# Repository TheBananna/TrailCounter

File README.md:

# TrailCounter
 A CV based trail counter I designed in a school group for the Friends of the Huckleberry Trail. Our final report can be found [here.](https://docs.google.com/document/d/190Tmrp1QDY-CEp3unXKZ8hlU1ujgZfHA_XcbUgvdIYQ/edit?usp=sharing)

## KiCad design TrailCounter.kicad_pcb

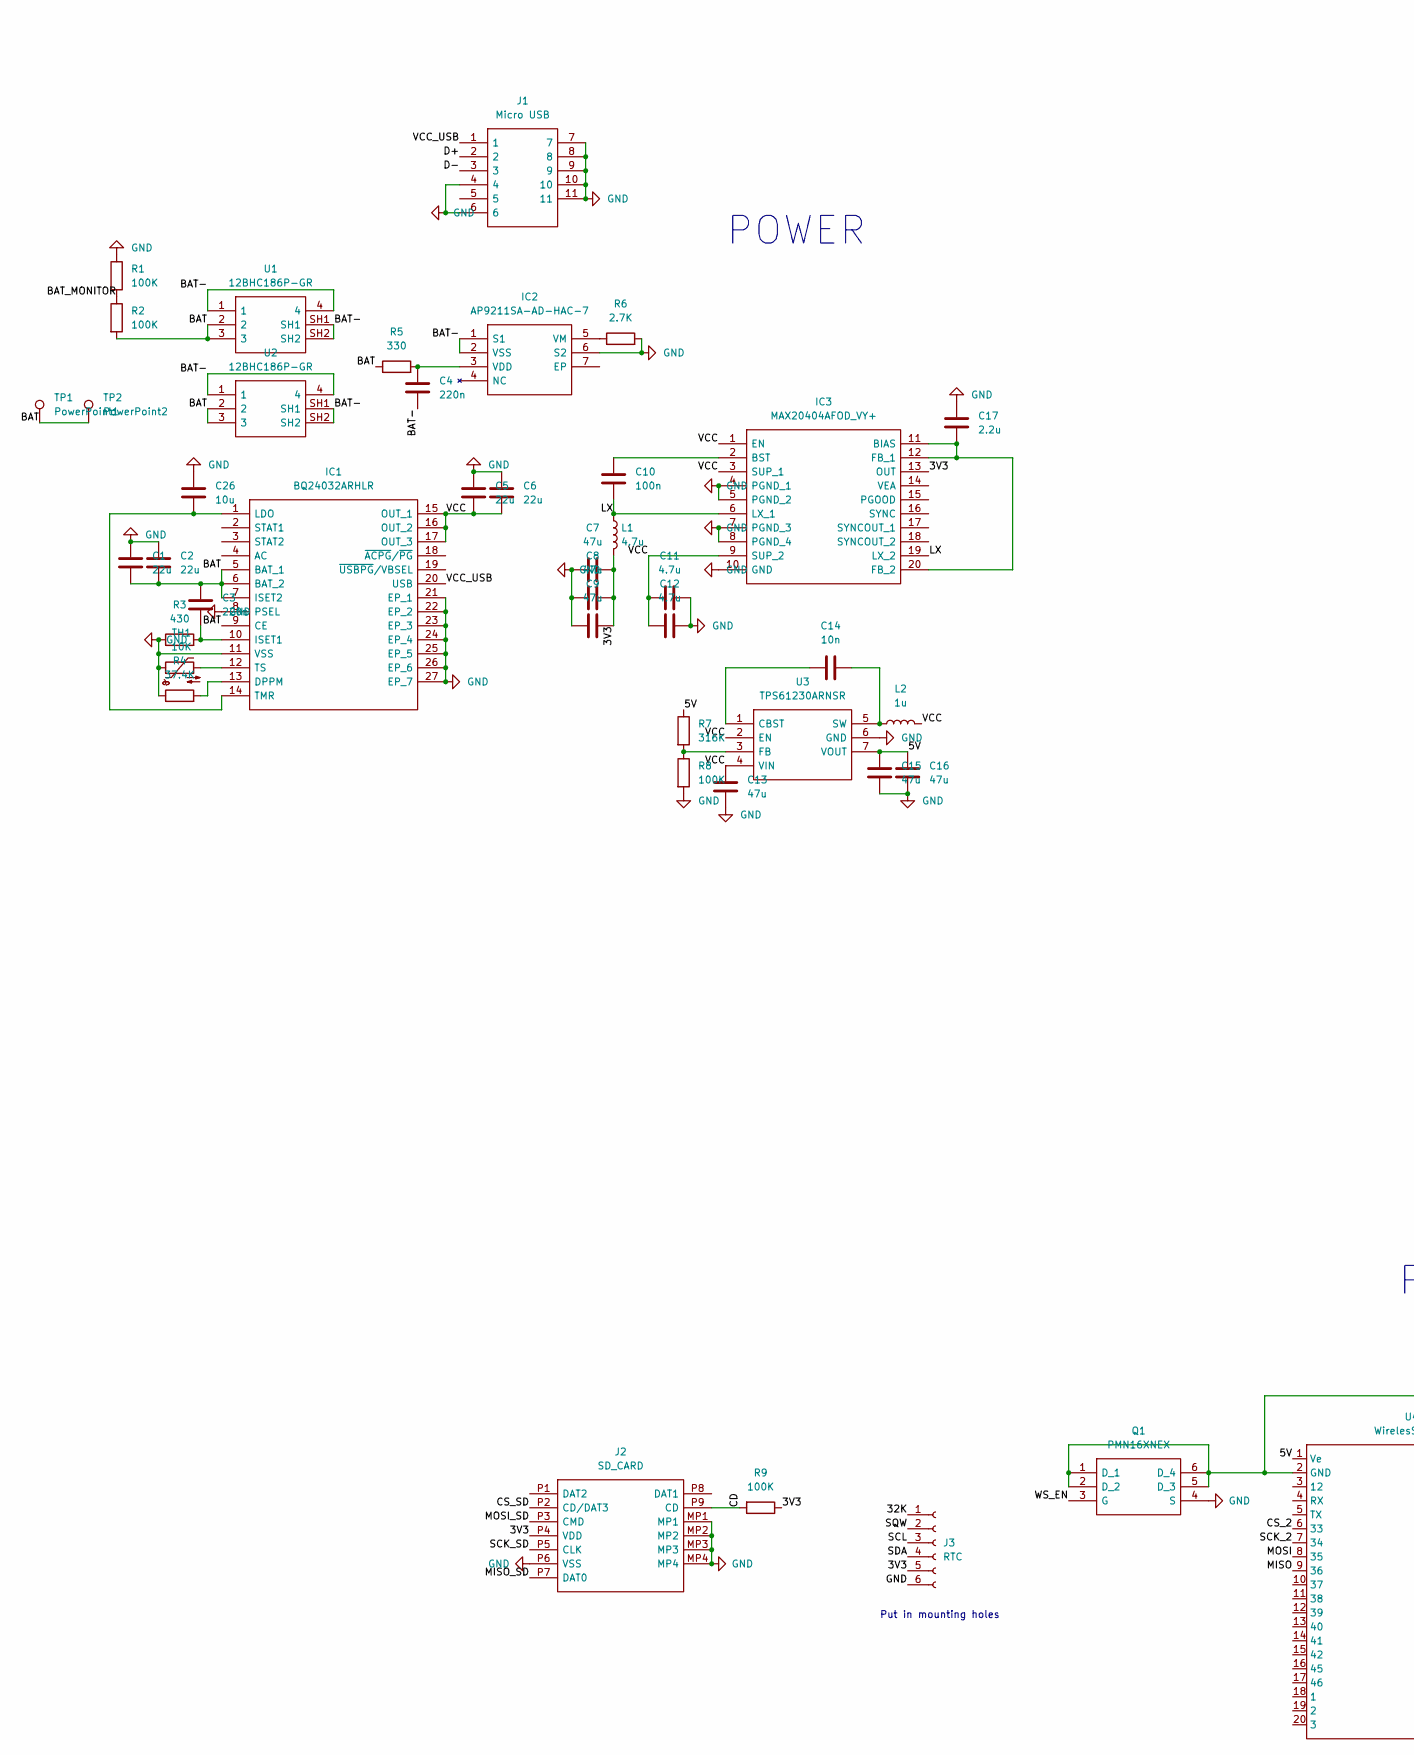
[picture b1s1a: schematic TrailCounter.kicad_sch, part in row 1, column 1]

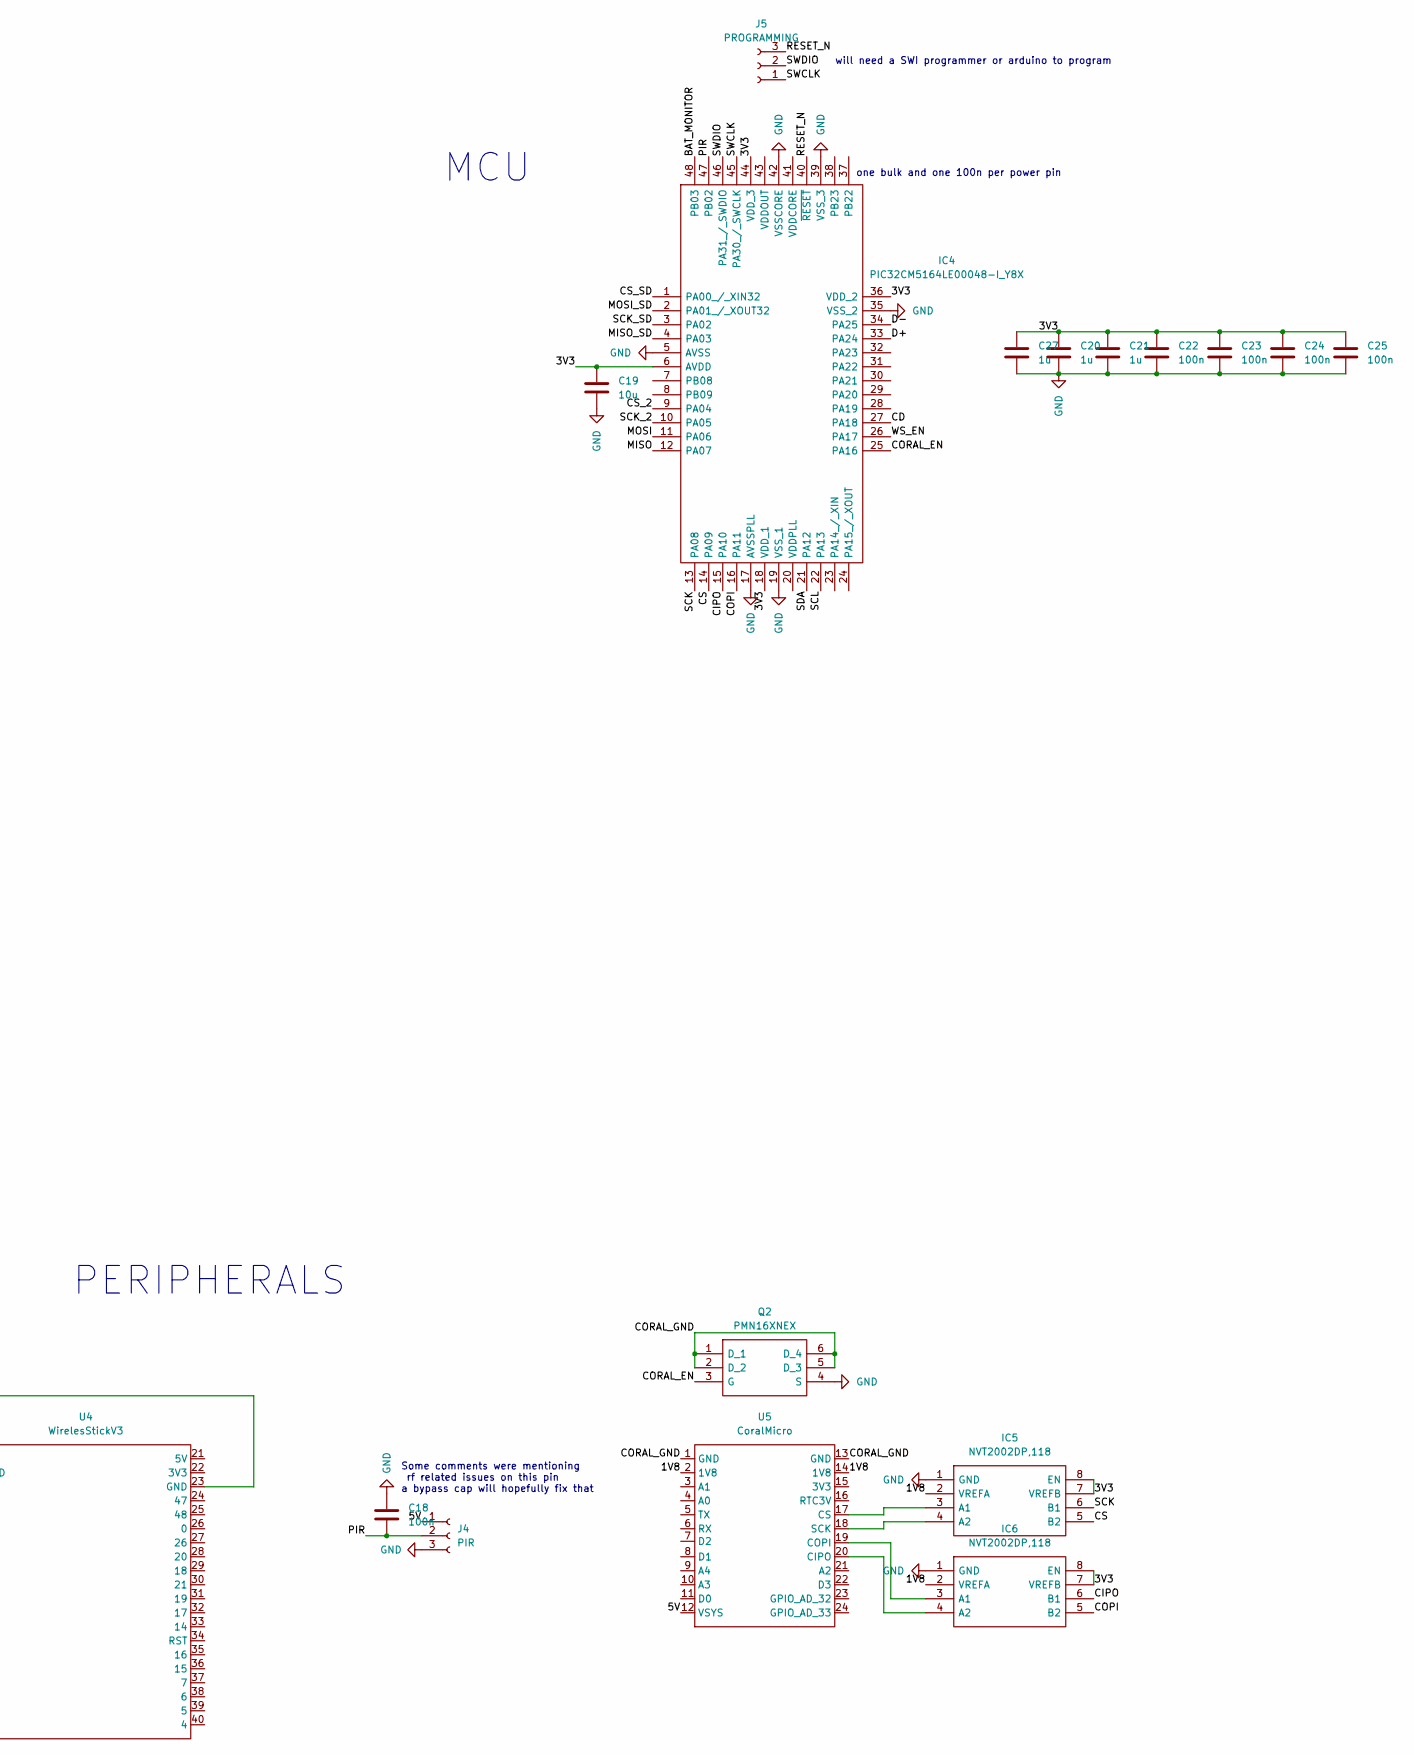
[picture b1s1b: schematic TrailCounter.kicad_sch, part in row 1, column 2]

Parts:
C1, C2, C5, C6: 22u; C_0805_2012Metric
C3, C4: 220n; C_0402_1005Metric
C7, C8, C9, C13, C15, C16: 47u; C_0805_2012Metric
C10, C18, C22, C23, C24, C25: 100n; C_0402_1005Metric
C11, C12: 4.7u; C_0603_1608Metric
C14: 10n; C_0402_1005Metric
C17: 2.2u; C_0603_1608Metric
C19, C26: 10u; C_0805_2012Metric
C20, C21, C27: 1u; C_0402_1005Metric
IC1: BQ24032ARHLR; MSP430FR2522IRHLR; Mouser Part Number 595-BQ24032ARHLR
IC2: AP9211SA-AD-HAC-7; AP9211SAADHAC7; Mouser Part Number 621-AP9211SA-AD-HAC7
IC3: MAX20404AFOD_VY+; MAX20404AFODVY; Mouser Part Number 700-MAX20404AFOD/VY+
IC4: PIC32CM5164LE00048-I_Y8X; QFP50P900X900X120-48N; Mouser Part Number 579-M5164LE00048IY8X
IC5, IC6: NVT2002DP,118; SOP65P490X110-8N; Mouser Part Number 771-NVT2002DP118
J1: Micro USB; UJ2WMIBH4SMTTR; Mouser Part Number 490-UJ2W-MIBH-4-SMT
J2: SD_CARD; MEM20750014001A; Mouser Part Number 640-MEM20750014001A
J3: RTC; PinHeader_1x06_P2.54mm_Vertical
J4: PIR; PinHeader_1x03_P2.54mm_Vertical
J5: PROGRAMMING; PinHeader_1x03_P2.54mm_Vertical
L1: 4.7u; L_12x12mm_H6mm
L2: 1u; L_1210_3225Metric
Q1, Q2: PMN16XNEX; SOT95P275X110-6N; Mouser Part Number 771-PMN16XNEX
R1, R2, R8: 100K; R_0402_1005Metric
R3: 430; R_0402_1005Metric
R4: 37.4K; R_0402_1005Metric
R5: 330; R_0603_1608Metric
R6: 2.7K; R_0402_1005Metric
R7: 316K; R_0402_1005Metric
R9: 100K; C_0402_1005Metric
TH1: 10K; R_0402_1005Metric
TP1: PowerPoint1; TestPoint_Pad_2.5x2.5mm
TP2: PowerPoint2; TestPoint_Pad_2.5x2.5mm
U1, U2: 12BHC186P-GR; 12BHC186PGR; Mouser Part Number 12BHC186P-GR
U3: TPS61230ARNSR; RNS0007A; Mouser Part Number 595-TPS61230ARNSR
U4: WirelesStickV3; WirelessStickV3
U5: CoralMicro

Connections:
/1V8: IC5.2 (VREFA), IC6.2 (VREFA), U5.2 (1V8), U5.14 (1V8)
/3V3: C7.1, C8.2, C9.2, C19.1, C20.1, C21.1, C22.1, C23.1, C24.1, C25.1, C27.1, IC3.13 (OUT), IC4.6 (AVDD), IC4.18 (VDD_1), IC4.36 (VDD_2), IC4.44 (VDD_3), IC5.7 (VREFB), IC5.8 (EN), IC6.7 (VREFB), IC6.8 (EN), J2.P4 (VDD), J3.5, L1.2, R9.1
/5V: C15.1, C16.1, J4.1, R7.1, U3.7 (VOUT), U4.1 (Ve), U5.12 (VSYS)
/32K: J3.1
/BAT: C1.1, C2.1, C3.1, IC1.5 (BAT_1), IC1.6 (BAT_2), IC1.7 (ISET2), IC1.9 (CE), R2.2, R5.1, TP1.1, TP2.1, U1.2, U1.3, U2.2, U2.3
/BAT-: C4.2, IC2.1 (S1), IC2.2 (VSS), U1.1, U1.4, U1.SH1, U1.SH2, U2.1, U2.4, U2.SH1, U2.SH2
/BAT_MONITOR: IC4.48 (PB03), R1.2, R2.1
/CD: IC4.27 (PA18), J2.P9 (CD), R9.2
/CIPO: IC4.15 (PA10), IC6.6 (B1)
/COPI: IC4.16 (PA11), IC6.5 (B2)
/CORAL_EN: IC4.25 (PA16), Q2.3 (G)
/CORAL_GND: Q2.1 (D_1), Q2.2 (D_2), Q2.5 (D_3), Q2.6 (D_4), U5.1 (GND), U5.13 (GND)
/CS: IC4.14 (PA09), IC5.5 (B2)
/CS_2: IC4.9 (PA04), U4.6 (33)
/CS_SD: IC4.1 (PA00_/_XIN32), J2.P2 (CD/DAT3)
/D+: IC4.33 (PA24), J1.2
/D-: IC4.34 (PA25), J1.3
/LX: C10.1, IC3.6 (LX_1), IC3.19 (LX_2), L1.1
/MISO: IC4.12 (PA07), U4.9 (36)
/MISO_SD: IC4.4 (PA03), J2.P7 (DAT0)
/MOSI: IC4.11 (PA06), U4.8 (35)
/MOSI_SD: IC4.2 (PA01_/_XOUT32), J2.P3 (CMD)
/PIR: C18.2, IC4.47 (PB02), J4.2
/RESET_N: IC4.40 (~RESET), J5.3
/SCK: IC4.13 (PA08), IC5.6 (B1)
/SCK_2: IC4.10 (PA05), U4.7 (34)
/SCK_SD: IC4.3 (PA02), J2.P5 (CLK)
/SCL: IC4.22 (PA13), J3.3
/SDA: IC4.21 (PA12), J3.4
/SQW: J3.2
/SWCLK: IC4.45 (PA30_/_SWCLK), J5.1
/SWDIO: IC4.46 (PA31_/_SWDIO), J5.2
/VCC: C5.1, C6.1, C11.1, C12.1, C13.1, IC1.15 (OUT_1), IC1.16 (OUT_2), IC1.17 (OUT_3), IC3.1 (EN), IC3.3 (SUP_1), IC3.9 (SUP_2), L2.2, U3.2 (EN), U3.4 (VIN)
/VCC_USB: IC1.20 (USB), J1.1
/WS_EN: IC4.26 (PA17), Q1.3 (G)
GND: C1.2, C2.2, C5.2, C6.2, C7.2, C8.1, C9.1, C11.2, C12.2, C13.2, C15.2, C16.2, C17.1, C18.1, C19.2, C20.2, C21.2, C22.2, C23.2, C24.2, C25.2, C26.2, C27.2, IC1.8 (PSEL), IC1.11 (VSS), IC1.21 (EP_1), IC1.22 (EP_2), IC1.23 (EP_3), IC1.24 (EP_4), IC1.25 (EP_5), IC1.26 (EP_6), IC1.27 (EP_7), IC2.6 (S2), IC3.4 (PGND_1), IC3.5 (PGND_2), IC3.7 (PGND_3), IC3.8 (PGND_4), IC3.10 (GND), IC4.5 (AVSS), IC4.17 (AVSSPLL), IC4.19 (VSS_1), IC4.35 (VSS_2), IC4.39 (VSS_3), IC4.42 (VSSCORE), IC5.1 (GND), IC6.1 (GND), J1.4, J1.6, J1.7, J1.8, J1.9, J1.10, J1.11, J2.MP1, J2.MP2, J2.MP3, J2.MP4, J2.P6 (VSS), J3.6, J4.3, Q1.4 (S), Q2.4 (S), R1.1, R3.1, R4.1, R6.2, R8.2, TH1.1, U3.6 (GND)
unnamed: C3.2, IC1.10 (ISET1), R3.2
unnamed: C4.1, IC2.3 (VDD), R5.2
unnamed: C10.2, IC3.2 (BST)
unnamed: C14.1, U3.1 (CBST)
unnamed: C14.2, L2.1, U3.5 (SW)
unnamed: C17.2, IC3.11 (BIAS), IC3.12 (FB_1), IC3.20 (FB_2)
unnamed: C26.1, IC1.1 (LDO), IC1.14 (TMR)
unnamed: IC1.12 (TS), TH1.2
unnamed: IC1.13 (DPPM), R4.2
unnamed: IC2.5 (VM), R6.1
unnamed: IC5.3 (A1), U5.17 (CS)
unnamed: IC5.4 (A2), U5.18 (SCK)
unnamed: IC6.3 (A1), U5.19 (COPI)
unnamed: IC6.4 (A2), U5.20 (CIPO)
unnamed: Q1.1 (D_1), Q1.2 (D_2), Q1.5 (D_3), Q1.6 (D_4), U4.2 (GND), U4.23 (GND)
unnamed: R7.2, R8.1, U3.3 (FB)

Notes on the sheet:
Some comments were mentioning rf related issues on this pin a bypass cap will hopefully fix that
will need a SWI programmer or arduino to program
POWER
one bulk and one 100n per power pin
MCU
PERIPHERALS
Put in mounting holes

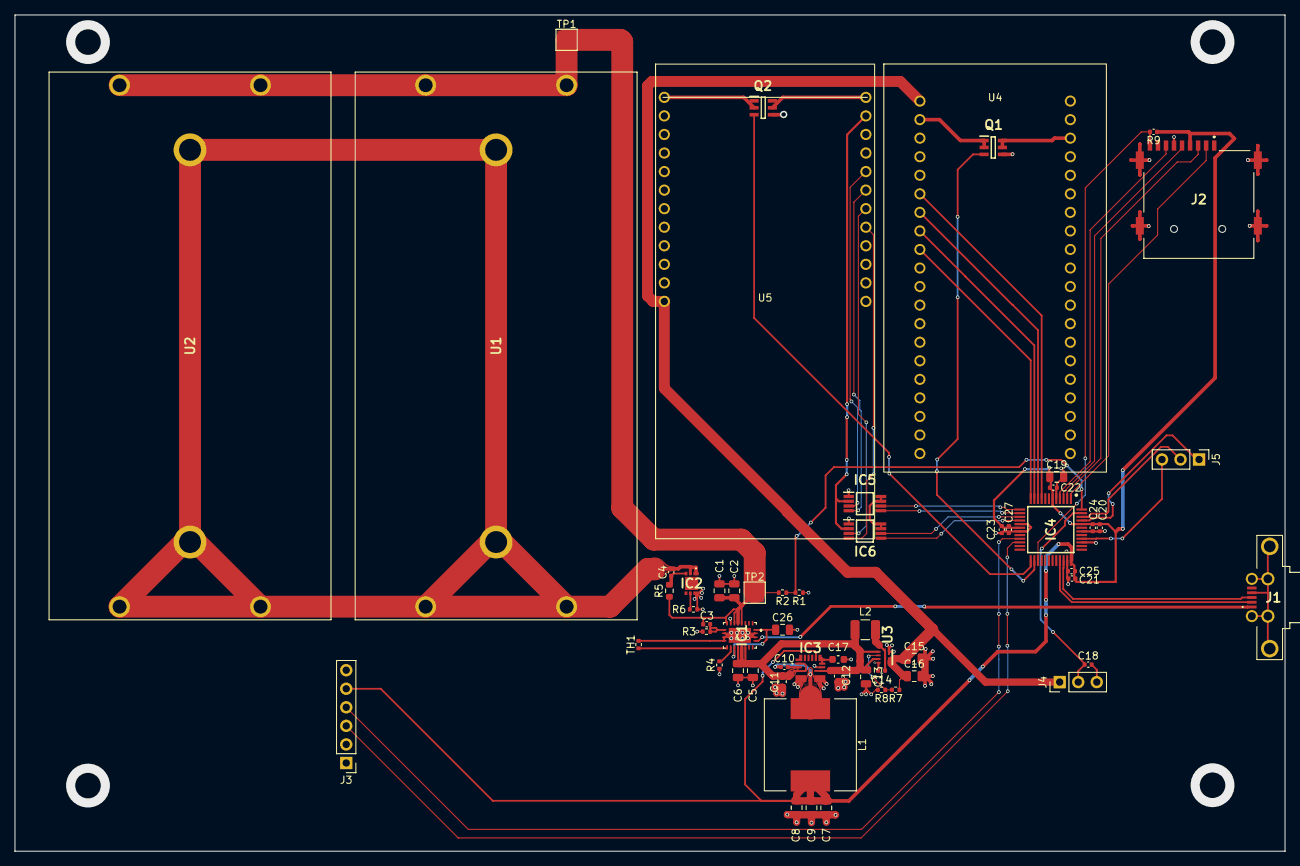
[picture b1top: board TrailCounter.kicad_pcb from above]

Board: 2 copper layers, 173.9 x 114.5 mm, 59 parts (0 on the bottom side), 50 nets.

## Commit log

2023-04-19 screenshot
